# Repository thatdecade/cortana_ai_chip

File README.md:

# Cortana AI Chip
Neopixel animated cortana chip with USB display stand.

Blog Post: https://www.westaby.net/2021/06/cortana-data-chip-and-display-stand/

Kits for sale: https://www.etsy.com/shop/WestabyElectronics

https://user-images.githubusercontent.com/6401110/123125386-17de3000-d40e-11eb-948b-370709867ea7.MOV

## Instructions: 
Choose which version you want to make, Trinket or Wemos.  Then print the associated 3D files and wire it up.

More build notes on the related pages.

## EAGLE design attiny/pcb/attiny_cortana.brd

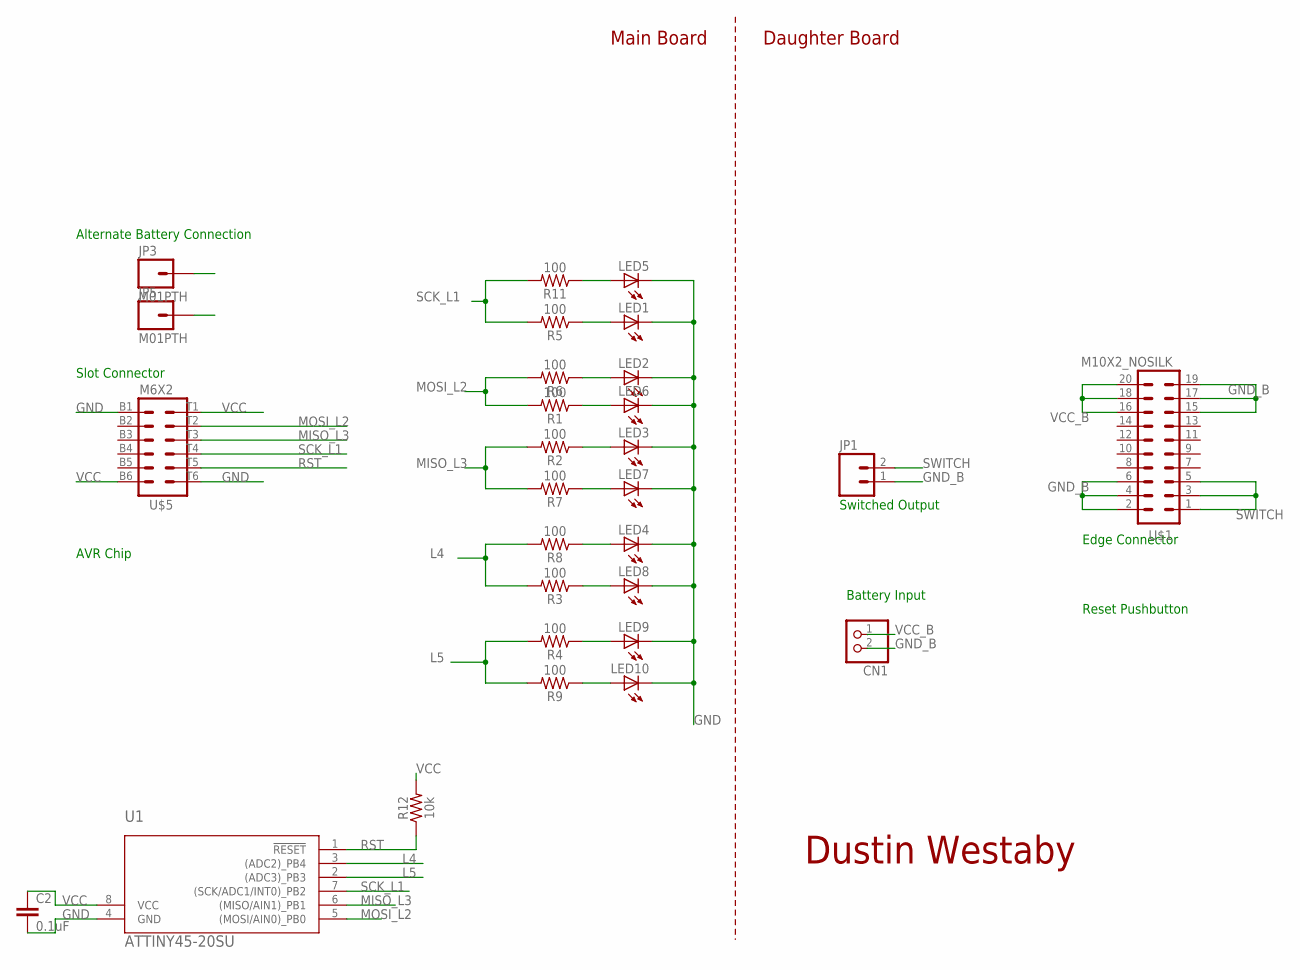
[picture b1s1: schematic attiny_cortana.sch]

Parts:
C2: 0.1uF; 0402-TIGHT
CN1: JST_2PIN-THM-RA; JST-PH-2-THM-RA
JP1: M02PTH; 1X02
JP3, JP5: M01PTH; 1X01
LED1, LED2, LED3, LED4, LED5, LED6, LED7, LED8, LED9, LED10: LED0603; LED-0603
R1, R2, R3, R4, R5, R6, R7, R8, R9, R11: 100; 0402-TIGHT
R12: 10k; 0402-TIGHT
U1: ATTINY45-20SU; 8S2_ATM
U$1: M10X2_NOSILK; 2X10_NOSILK
U$5: M6X2; CRT_CON

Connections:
GND: C2.2, JP5.1, LED1.C, LED2.C, LED3.C, LED4.C, LED5.C, LED6.C, LED7.C, LED8.C, LED9.C, LED10.C, U1.4 (GND), U$5.B1 (1), U$5.T6 (12)
GND_B: CN1.2 (1), JP1.1, U$1.2, U$1.4, U$1.6, U$1.15, U$1.17, U$1.19
L4: R3.2, R8.2, U1.3 ((ADC2)_PB4)
L5: R4.2, R9.2, U1.2 ((ADC3)_PB3)
MISO_L3: R2.2, R7.2, U1.6 ((MISO/AIN1)_PB1), U$5.T3 (9)
MOSI_L2: R1.2, R6.2, U1.5 ((MOSI/AIN0)_PB0), U$5.T2 (8)
unnamed: LED3.A, R2.1
unnamed: LED4.A, R8.1
unnamed: LED1.A, R5.1
unnamed: LED6.A, R1.1
unnamed: LED2.A, R6.1
unnamed: LED5.A, R11.1
unnamed: LED7.A, R7.1
unnamed: LED8.A, R3.1
unnamed: LED9.A, R4.1
unnamed: LED10.A, R9.1
RST: R12.1, U1.1 (!RESET), U$5.T5 (11)
SCK_L1: R5.2, R11.2, U1.7 ((SCK/ADC1/INT0)_PB2), U$5.T4 (10)
SWITCH: JP1.2, U$1.1, U$1.3, U$1.5
VCC: C2.1, JP3.1, R12.2, U1.8 (VCC), U$5.B6 (6), U$5.T1 (7)
VCC_B: CN1.1 (2), U$1.16, U$1.18, U$1.20

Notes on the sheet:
Dustin Westaby
Slot Connector
Switched Output
Battery Input
Daughter Board
Main Board
Alternate Battery Connection
AVR Chip
Reset Pushbutton
Edge Connector

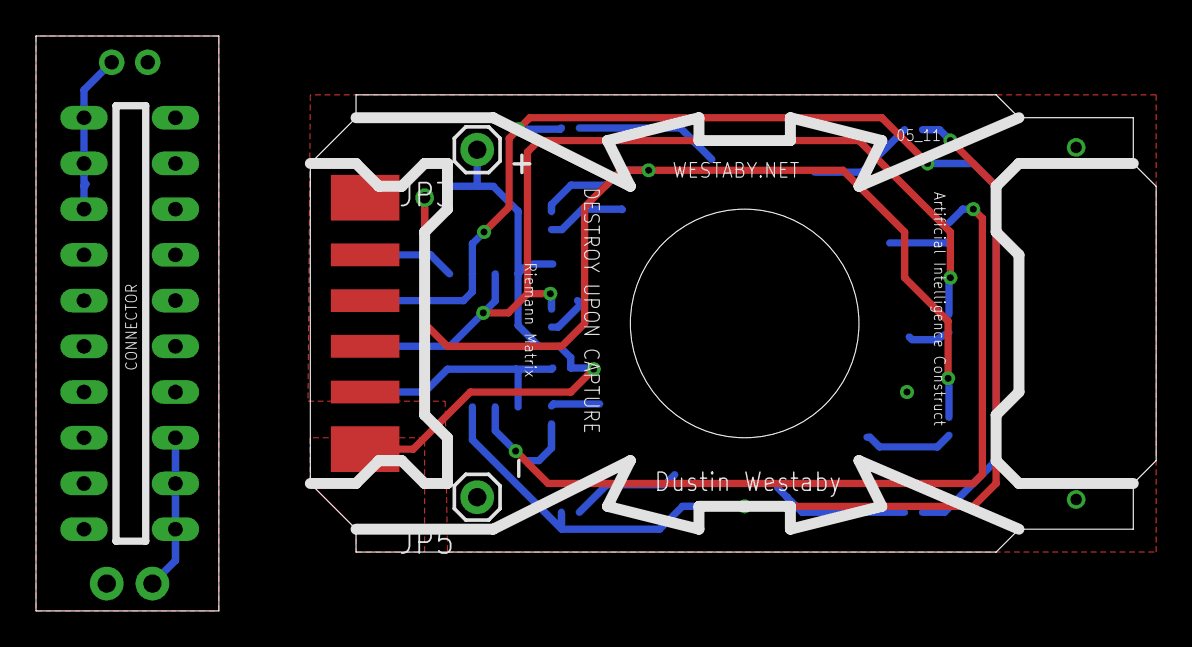
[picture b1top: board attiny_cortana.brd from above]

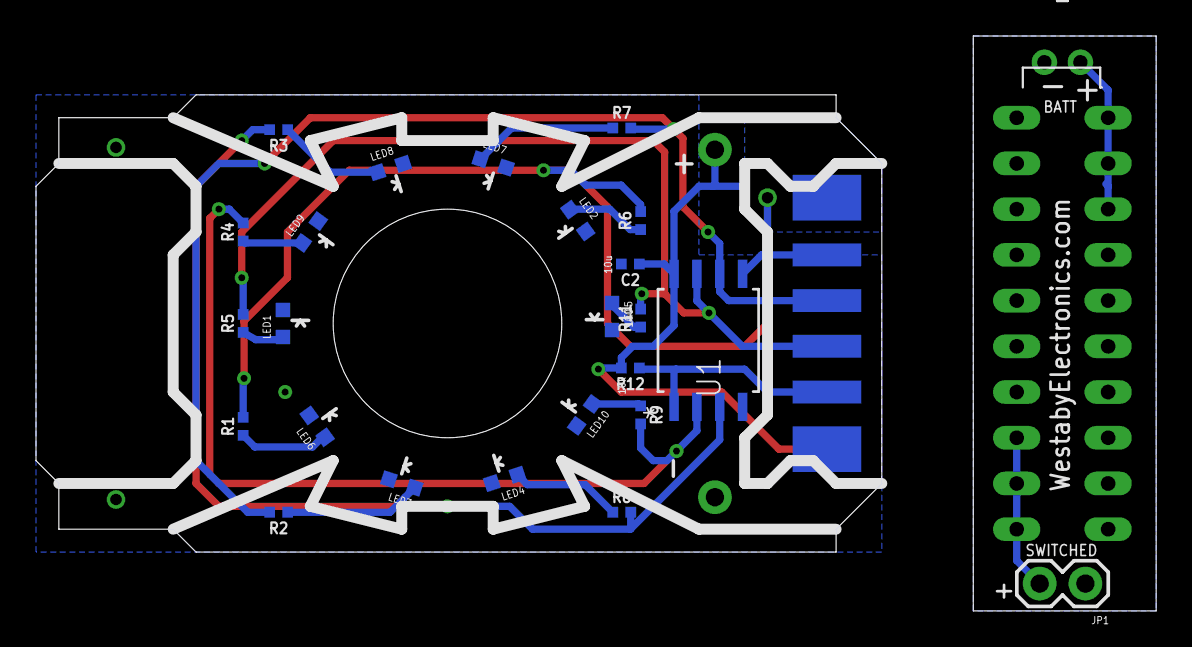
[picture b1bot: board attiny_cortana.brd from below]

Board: 2 copper layers, 62.2 x 31.9 mm, 29 parts (26 on the bottom side), 21 nets.

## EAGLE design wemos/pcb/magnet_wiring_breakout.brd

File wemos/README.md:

# WORK IN PROGRESS!!!!

I have not built this version yet.

# Wemos Build Instructions

This folder is for building a Cortana AI Chip with an WEMOS D1 Mini dev board.

[IMAGE]

## Part List:
* WEMOS D1 Mini https://amzn.to/3qwWNKp
* Neopixel jewel https://amzn.to/3gKQ6ko
* Pushbutton https://amzn.to/3x0Akra
* Magnet Connectors [TBD]

* Silver PLA Filament https://amzn.to/3vN5HnV
* Gray Glitter PLA Filament https://amzn.to/3d2W3ab
* Transparent PLA Filament https://amzn.to/3xEOMFm

We are a participant in the Amazon Services LLC Associates Program, an affiliate advertising program designed to provide a means for us to earn fees by linking to Amazon.com and affiliated sites.

## 3D Printing:

The Cortana Data Chip’s 3D model was designed by Dylan Powell. I modified the Halo Cortana Chip to fit the neopixel jewel and magnet pin connector. Model is prescaled to 125%. Download: https://www.thingiverse.com/thing:4891701

I printed the Data Chip with 0.20 layer height as a color change job at 2.80mm. Dark grey and then Silver.

## Assembly and Wiring:
* WEMOS D0 to Neopixel Data In
* WEMOS D1 to Button LED
* WEMOS D2 to Button Switch

The magnet connector has straight pins (not solder cup friendly).  Recommend using some spare perfboard as a breakout or some 30 AWG Wrapping Wire around the pins using a wire wrap tool, then soldering.  More info: https://learn.sparkfun.com/tutorials/working-with-wire/how-to-use-a-wire-wrap-tool

Since the magnet connector is not keyed, it is possible to connect the cortana ai chip in backwards and reverse all the pins to the neopixel.  To prevent burnout, place the V+ pin in the center and a 100k ohm resistor on the data pin.  The breakout board in the pcb folder does this.

## Arduino:

TBD

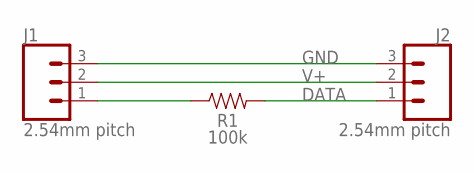
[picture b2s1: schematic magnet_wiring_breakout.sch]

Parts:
J1, J2: 2.54mm pitch; 1X03
R1: 100k; 0805

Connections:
DATA: J2.1, R1.2
GND: J1.3, J2.3
unnamed: J1.1, R1.1
V+: J1.2, J2.2

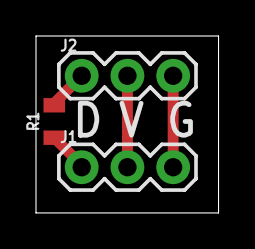
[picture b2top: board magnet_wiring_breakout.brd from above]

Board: 2 copper layers, 10.1 x 9.8 mm, 3 parts (0 on the bottom side), 4 nets.

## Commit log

2021-06-23 3D files
2021-06-23 Arduino files
2021-06-23 images
2021-06-24 Magnet breakout pcb
2021-08-24 Attiny ring design
2021-12-14 3D parts for D1 Mini and magnet connector
2022-07-11 attiny stand
2022-07-11 rename

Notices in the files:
parts and their libraries:
SparkFun-Resistors: Licensing: Creative Commons ShareAlike 4.0 International - https://creativecommons.org/licenses/by-sa/4.0
COPYRIGHT: Copyright (C) 2021 Ultra Librarian. All rights reserved.
